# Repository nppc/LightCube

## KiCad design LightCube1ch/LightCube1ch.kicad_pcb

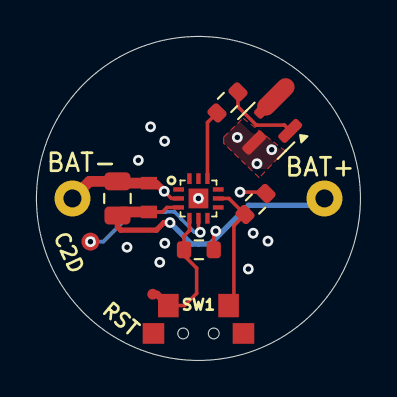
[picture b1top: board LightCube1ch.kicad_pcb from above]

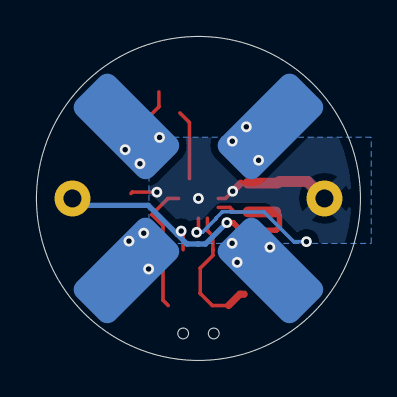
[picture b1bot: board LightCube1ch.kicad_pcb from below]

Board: 2 copper layers, 18.0 x 18.0 mm, 16 parts (4 on the bottom side), 8 nets.

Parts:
C1: 100n; C_0603
C3: 2uf; C_0805_2012Metric
J1, J2, J3, J4: C_LED; PAD3x6
J5: BAT+; Conn-1pinD1.0mm
J6: BAT-; Conn-1pinD1.0mm
J7: C2D; Test_PAD_0.6
J8: RST; Test_PAD_0.6
Q1: AO3400A; SOT-23
R1: 2K; R_0603_1608Metric
R2: 15K; R_0603_1608Metric
R3: 12; R_0603_1608Metric
SW1: SW_Push; Button_TS-018
U1: EFM8BB50-QFN12; QFN12-2x2

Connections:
/BUT_SENSE: R2.1, SW1.1, U1.8 (P0.5)
/C2D: J7.1, U1.5 (P1.0/C2D)
/Q1: R3.1, U1.10 (P0.3)
/RST: J8.1, R1.2, SW1.2, U1.4 (RSTb/C2CK)
GND: C1.2, C3.2, J6.1, Q1.2 (S), R2.2, U1.2 (GND), U1.13 (GND)
unnamed: J1.1, Q1.3 (D)
unnamed: Q1.1 (G), R3.2
VDD: C1.1, C3.1, J5.1, R1.1, U1.3 (VDD)

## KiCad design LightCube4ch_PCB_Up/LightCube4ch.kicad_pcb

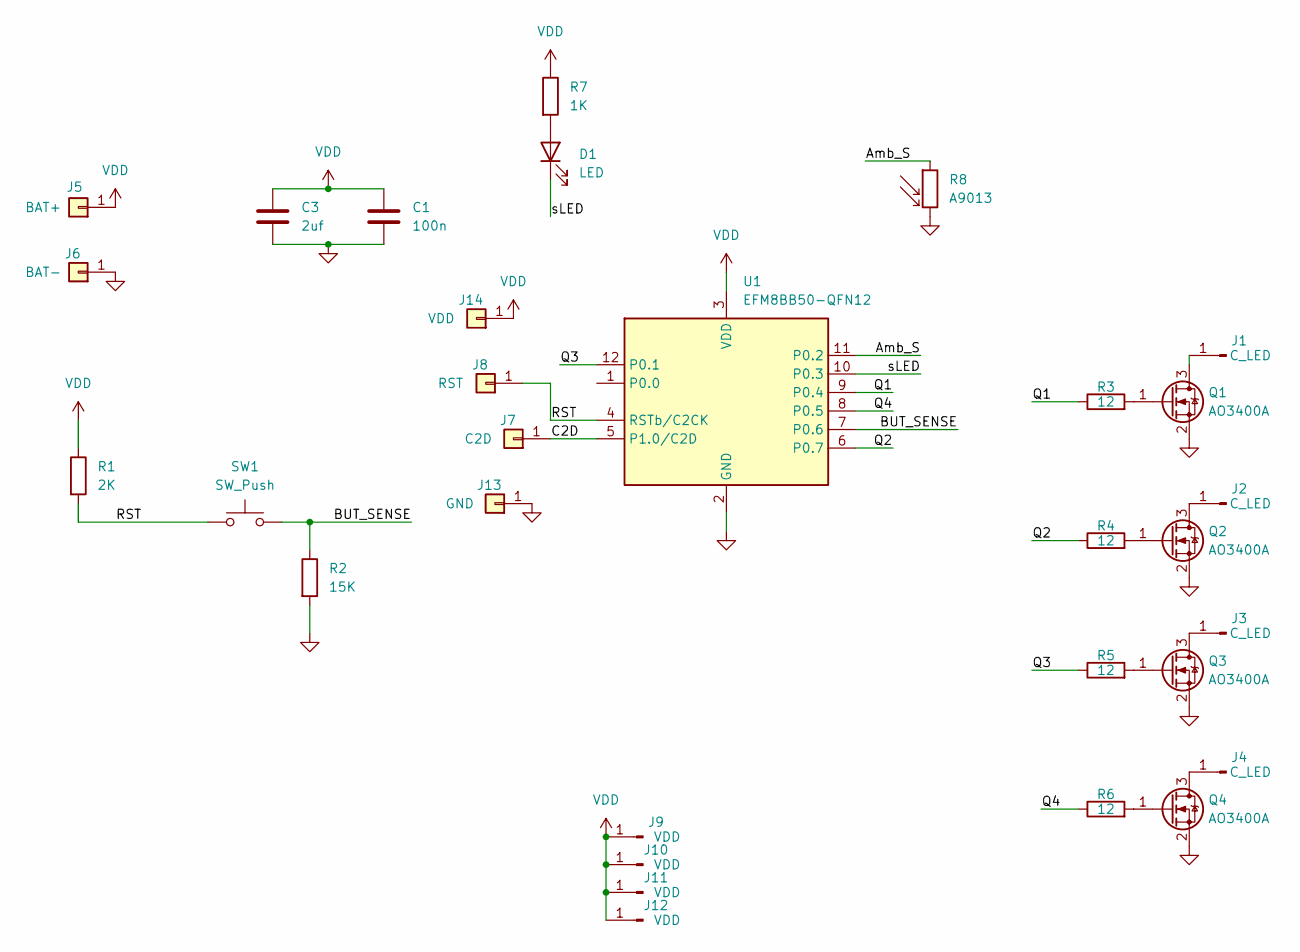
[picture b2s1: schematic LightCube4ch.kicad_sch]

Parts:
C1: 100n; C_0603
C3: 2uf; C_0805_2012Metric
D1: LED; LED_0603_1608Metric_Pad1.05x0.95mm_HandSolder
J1, J2, J3, J4: C_LED; Pin3.5mm
J5: BAT+; PAD_3x5
J6: BAT-; Pin2.5mm
J7: C2D; PAD_1.2X0.6_Round
J8: RST; PAD_1.2X0.6_Round
J9, J10, J11, J12: VDD; Pad_3.5x7mm
J13: GND; PAD_1.2X0.6_Round
J14: VDD; PAD_1.2X0.6_Round
Q1, Q2, Q3, Q4: AO3400A; SOT-23
R1: 2K; R_0603_1608Metric
R2: 15K; R_0603_1608Metric
R3, R4, R5, R6: 12; R_0603_1608Metric
R7: 1K; R_0603_1608Metric
R8: A9013; R_LDR_5.0x4.1mm_P3mm_Vertical
SW1: SW_Push; Button_TS-018
U1: EFM8BB50-QFN12; QFN12-2x2

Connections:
/Amb_S: R8.1, U1.11 (P0.2)
/BUT_SENSE: R2.1, SW1.2, U1.7 (P0.6)
/C2D: J7.1, U1.5 (P1.0/C2D)
/Q1: R3.1, U1.9 (P0.4)
/Q2: R4.1, U1.6 (P0.7)
/Q3: R5.1, U1.12 (P0.1)
/Q4: R6.1, U1.8 (P0.5)
/RST: J8.1, R1.2, SW1.1, U1.4 (RSTb/C2CK)
/sLED: D1.1 (K), U1.10 (P0.3)
GND: C1.2, C3.2, J6.1, J13.1, Q1.2 (S), Q2.2 (S), Q3.2 (S), Q4.2 (S), R2.2, R8.2, U1.2 (GND), U1.13 (GND)
unnamed: D1.2 (A), R7.2
unnamed: J1.1, Q1.3 (D)
unnamed: J2.1, Q2.3 (D)
unnamed: J3.1, Q3.3 (D)
unnamed: J4.1, Q4.3 (D)
unnamed: Q1.1 (G), R3.2
unnamed: Q2.1 (G), R4.2
unnamed: Q3.1 (G), R5.2
unnamed: Q4.1 (G), R6.2
VDD: C1.1, C3.1, J5.1, J9.1, J10.1, J11.1, J12.1, J14.1, R1.1, R7.1, U1.3 (VDD)

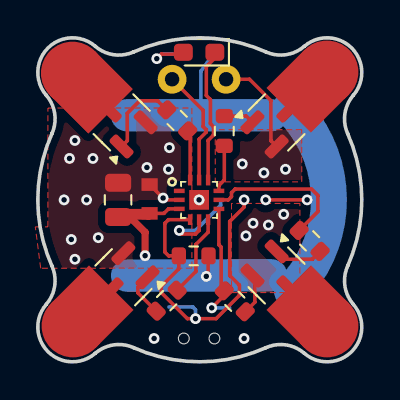
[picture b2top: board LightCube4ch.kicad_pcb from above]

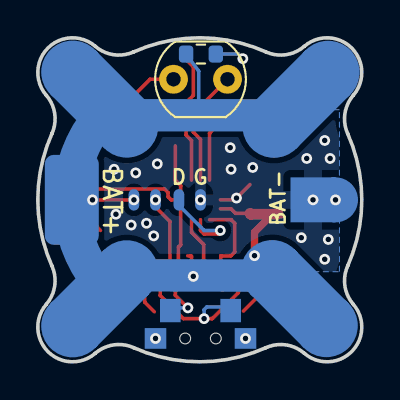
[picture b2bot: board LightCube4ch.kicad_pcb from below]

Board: 2 copper layers, 18.0 x 18.0 mm, 31 parts (13 on the bottom side), 20 nets.

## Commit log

2025-10-03 working simple version
2025-10-05 fade out is added
2025-10-19 add brightness
2025-10-20 ambient brightness read fix
2025-11-17 safety check for candle effect
